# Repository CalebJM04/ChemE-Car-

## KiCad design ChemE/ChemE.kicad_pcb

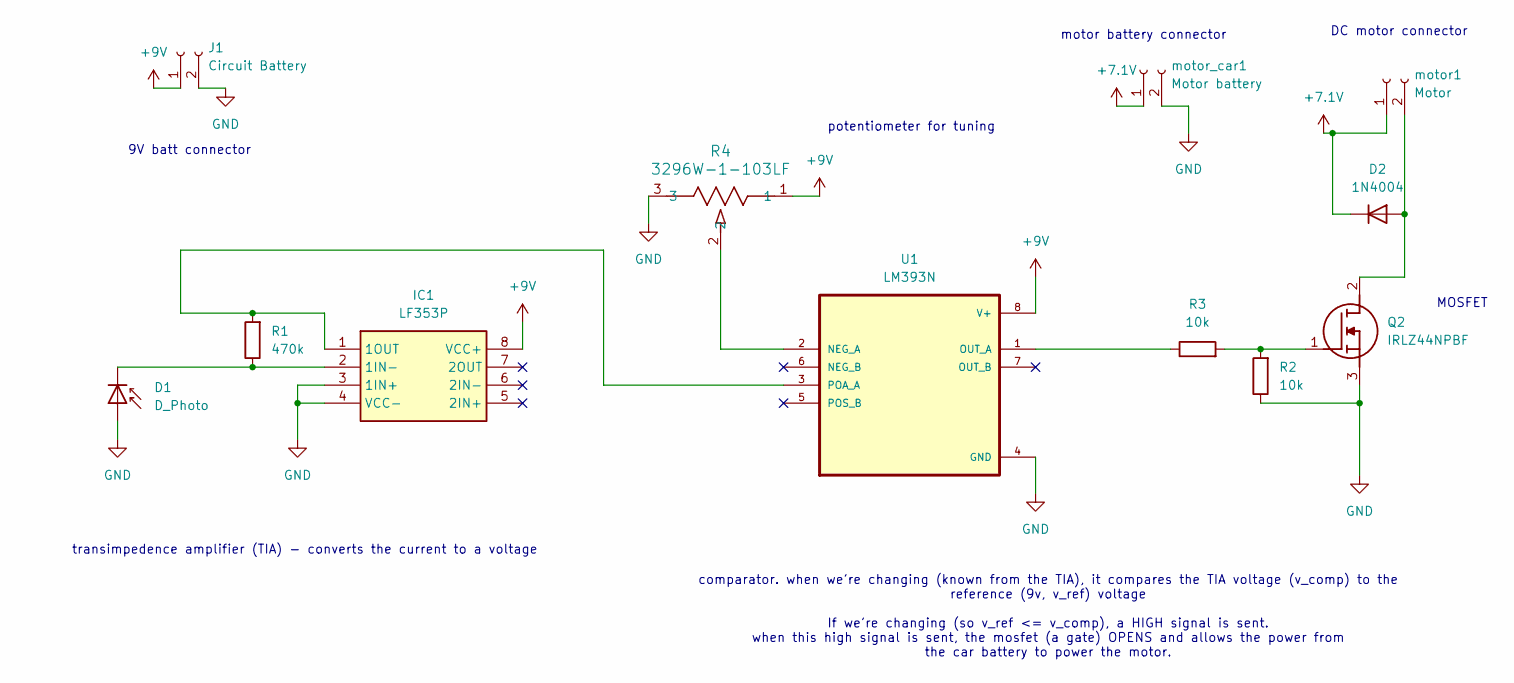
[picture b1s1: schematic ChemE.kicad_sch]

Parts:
D1: D_Photo; Osram_BPW82
D2: 1N4004; D_DO-41_SOD81_P10.16mm_Horizontal
IC1: LF353P; DIP794W53P254L959H508Q8N; Mouser Part Number 595-LF353P
J1: Circuit Battery; PinHeader_1x02_P2.54mm_Vertical
Q2: IRLZ44NPBF; TO254P469X1042X1967-3P; Mouser Part Number 942-IRLZ44NPBF
R1: 470k; R_Axial_DIN0204_L3.6mm_D1.6mm_P2.54mm_Vertical
R2, R3: 10k; R_Axial_DIN0204_L3.6mm_D1.6mm_P2.54mm_Vertical
R4: 3296W-1-103LF; POT_3296W
U1: LM393N; DIP794W45P254L959H508Q8
motor1: Motor; PinHeader_1x02_P2.54mm_Vertical
motor_car1: Motor battery; PinHeader_1x02_P2.54mm_Vertical

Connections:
+7.1V: D2.1 (K), motor1.1, motor_car1.1
+9V: IC1.8 (VCC+), J1.1, R4.1, U1.8 (V+)
GND: D1.2 (A), IC1.3 (1IN+), IC1.4 (VCC-), J1.2, Q2.3 (S), R2.1, R4.3, U1.4 (GND), motor_car1.2
unnamed: D1.1 (K), IC1.2 (1IN-), R1.1
unnamed: D2.2 (A), Q2.2 (D), motor1.2
unnamed: IC1.1 (1OUT), R1.2, U1.3 (POA_A)
unnamed: Q2.1 (G), R2.2, R3.2
unnamed: R4.2, U1.2 (NEG_A)
unnamed: R3.1, U1.1 (OUT_A)

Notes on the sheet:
potentiometer for tuning
transimpedence amplifier (TIA) - converts the current to a voltage
motor battery connector
DC motor connector
MOSFET
comparator. when we're changing (known from the TIA), it compares the TIA voltage (v_comp) to the reference (9v, v_ref) voltage If we're changing (so v_ref <= v_comp), a HIGH signal is sent. when this high signal is sent, the mosfet (a gate) OPENS and allows the power from the car battery to power 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
9V batt connector

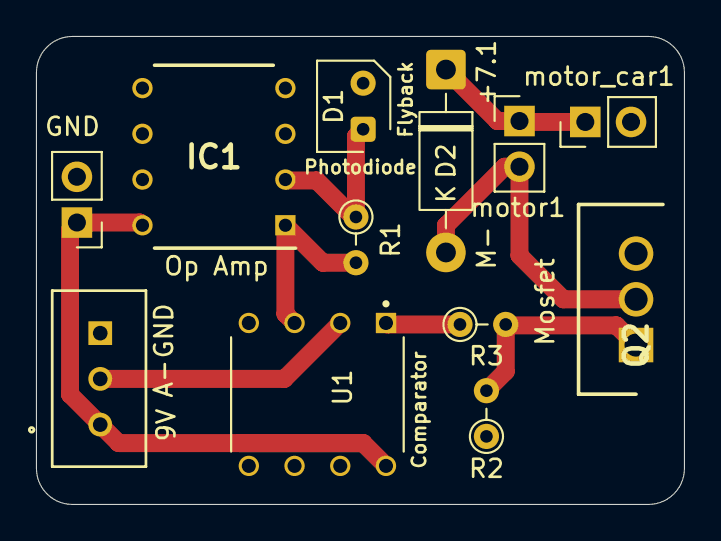
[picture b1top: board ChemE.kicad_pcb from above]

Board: 2 copper layers, 36.0 x 26.0 mm, 12 parts (0 on the bottom side), 9 nets.

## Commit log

2025-11-13 finished sch
2025-11-13 finished pcb
2025-11-13 made prod
2025-11-13 updated sch to have all tht. added 1n004
    pcb has not been updated yet. last push has last sch and pcb with the smd resistors.
2025-11-13 increased trace width, made tht
    increased trace width from .5mm to 1mm and made everything THT.
2025-11-13 annoted the sch
2025-11-13 made prod. $7.25
2025-11-13 redid pot with correct wiring
    https://www.piher.net/wp-content/uploads/PIHER_PT-15_PTC-15.pdf
    also made prod. should be good to order.
2025-11-13 slight routing.
2025-11-14 done
2025-11-14 made prod w/ rounded corners. ordered
2025-11-14 added my name. ordered
2025-11-14 ordered
2026-01-04 updated design w/ new components and footprints
2026-01-04 made prod w/ new components and ordered
2026-01-05 ordered and closed
